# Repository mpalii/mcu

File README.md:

# MCUs

***ATmega8/*** folder is a multi-project solution for Microchip Studio IDE (Atmel Studio). Open the ***ATmega8.atsln*** file in Microchip Studio IDE (Atmel Studio), then rebuild the solution and all included projects will be ready to work.

### MCUs datasheets and documentation
- [ATmega8(L)](https://ww1.microchip.com/downloads/en/DeviceDoc/Atmel-2486-8-bit-AVR-microcontroller-ATmega8_L_datasheet.pdf)  
- [ATmega48A/PA/88A/PA/168A/PA/328/P](https://ww1.microchip.com/downloads/en/DeviceDoc/ATmega48A-PA-88A-PA-168A-PA-328-P-DS-DS40002061B.pdf)  
- [ATmega328P](https://ww1.microchip.com/downloads/en/DeviceDoc/Atmel-7810-Automotive-Microcontrollers-ATmega328P_Datasheet.pdf)  
- [AVR Instruction Set Manual](http://ww1.microchip.com/downloads/en/devicedoc/atmel-0856-avr-instruction-set-manual.pdf)  

### Troubleshoot  
#### 1. USBASP driver for Windows 10  
Operating system Windows requires driver for USBASP programmer. It is possible to use [libusb-win32](https://sourceforge.net/projects/libusb-win32/ "libusb-win32"), [libusbK](https://sourceforge.net/projects/libusbk/ "libusbK") or [Zadig](https://zadig.akeo.ie/ "Zadig"). Long story short, all these solutions install generic USB drivers.  
For 'libusbK': *step-1* download and install 'UsbK Development Kit' application; *step-2* plug USBASP programmer to USB; *step-3* launch 'Driver Install Creator Wizard'; *step-4* select 'libusbK' kernel driver package for target device and generate driver package; *step-5* install newly created driver from 'DriverPackages' folder; *step-6* remove 'UsbK Development Kit' and 'DriverPackages' folder.  
#### 2. USBASP connectivity issue with AVRdude  
Rootcause is a high internal clock frequency of a programmer. *First solution* is to specify baudrate with a '-B' flag:  
`avrdude -c usbasp -p m328p -B3` - this will set SCK frequency to 187500 Hz.  
*Second solution* is to close jumper JP3 in the USBASP device. No flags for avrdude is need in this case.  
#### 3. Visual Studio Code configuration  
To prepare VSC for working with avr-toolchai:  
- go to IntelliSense Configurations  
- hit the 'Add Configuration' button, type new configuration name (e.g. AVR) and hit 'Ok'  
- update 'Compiler path' input field with: *{path prefix}\toolchain\avr8\avr8-gnu-toolchain\bin\avr-gcc.exe*  
- add path to the 'Include path' input field: *{path prefix}/toolchain/avr8/avr8-gnu-toolchain/avr/include/\*\**  
- add *__AVR_ATmega328P__* to 'Defines' section  
#### 4. Atmel/Microchip Studio line numbers  
To show line numbers in A/M Studio go to **'Tools' -> 'Options' -> 'Text Editor' -> 'All Language'** and toggle **Line numbers** checkbox in the **Settings** section  

// TODO
https://avrdudes.github.io/avr-libc/avr-libc-user-manual/install_tools.html  
https://kleinembedded.com/stm32-without-cubeide-part-1-the-bare-necessities/#comment-37  
https://www.youtube.com/watch?v=7YhRFx-oyW4&list=PL3BR09unfgchRxdDws74aY4mlSk9eYGEs  
https://www.youtube.com/watch?v=MhOba73z-dQ&pp=ygUMYXJ0ZnVsIGJ5dGVz

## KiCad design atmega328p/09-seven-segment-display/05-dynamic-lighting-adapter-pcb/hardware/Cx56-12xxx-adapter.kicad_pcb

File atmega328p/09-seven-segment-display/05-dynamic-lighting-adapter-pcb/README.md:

### Example 05 - Cx56-12xxx adapter

PCB top:  

PCB bottom:  

Device:  

### Useful links

- [How to generate Gerber and Drill files in KiCad 7](https://jlcpcb.com/help/article/362-how-to-generate-gerber-and-drill-files-in-kicad-7)  
- [KiCAD 7 PCB Layout in 5 steps](https://www.youtube.com/watch?v=3FGNw28xBr0)

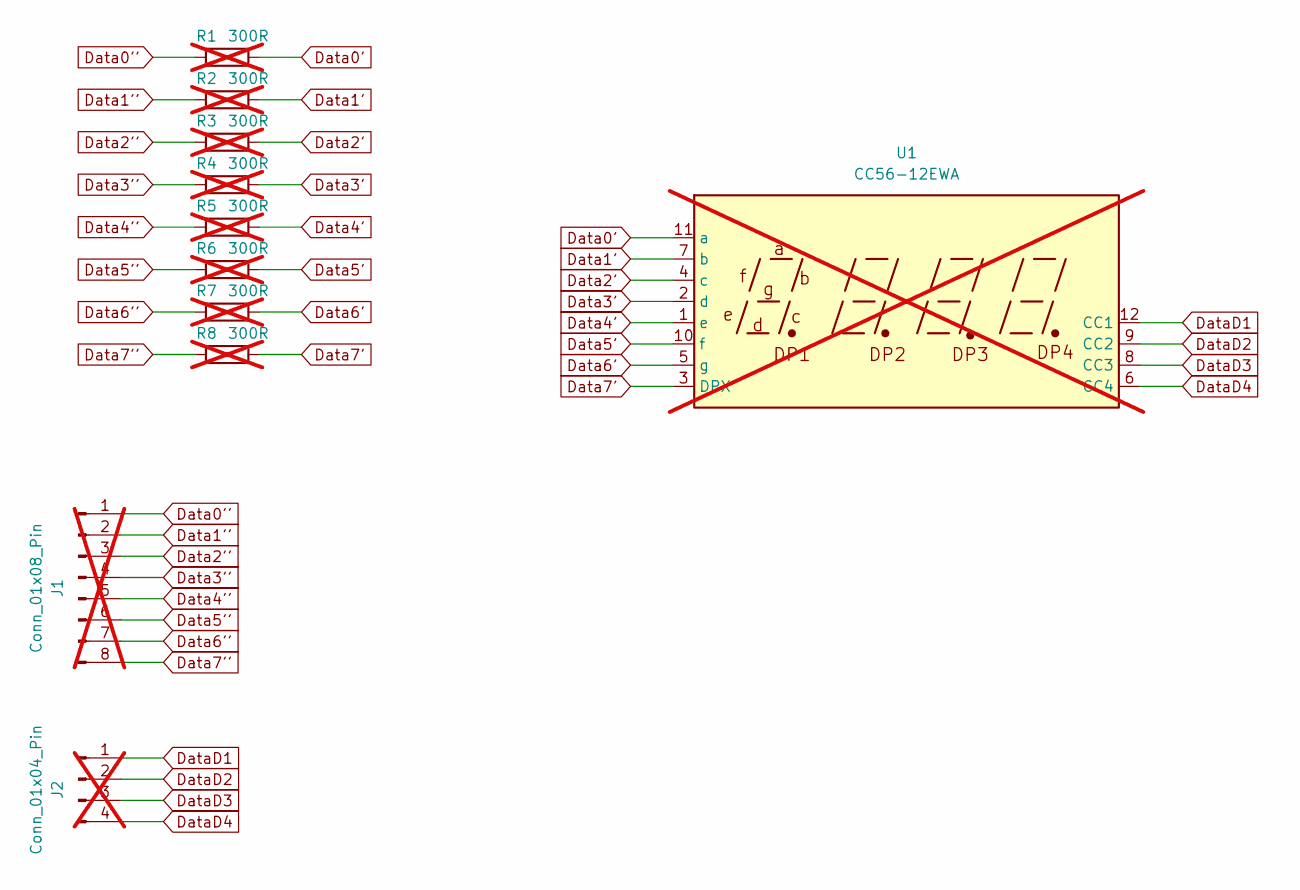
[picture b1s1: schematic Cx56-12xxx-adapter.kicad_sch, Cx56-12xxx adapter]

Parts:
J1: Conn_01x08_Pin; PinHeader_1x08_P2.54mm_Vertical; not fitted
J2: Conn_01x04_Pin; PinHeader_1x04_P2.54mm_Vertical; not fitted
R1, R2, R3, R4, R5, R6, R7, R8: 300R; R_0805_2012Metric_Pad1.20x1.40mm_HandSolder; not fitted
U1: CC56-12EWA; CA56-12EWA; not fitted

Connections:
Data0': R1.1, U1.11 (a)
Data0'': J1.1, R1.2
Data1': R2.1, U1.7 (b)
Data1'': J1.2, R2.2
Data2': R3.1, U1.4 (c)
Data2'': J1.3, R3.2
Data3': R4.1, U1.2 (d)
Data3'': J1.4, R4.2
Data4': R5.1, U1.1 (e)
Data4'': J1.5, R5.2
Data5': R6.1, U1.10 (f)
Data5'': J1.6, R6.2
Data6': R7.1, U1.5 (g)
Data6'': J1.7, R7.2
Data7': R8.1, U1.3 (DPX)
Data7'': J1.8, R8.2
DataD1: J2.1, U1.12 (CC1)
DataD2: J2.2, U1.9 (CC2)
DataD3: J2.3, U1.8 (CC3)
DataD4: J2.4, U1.6 (CC4)

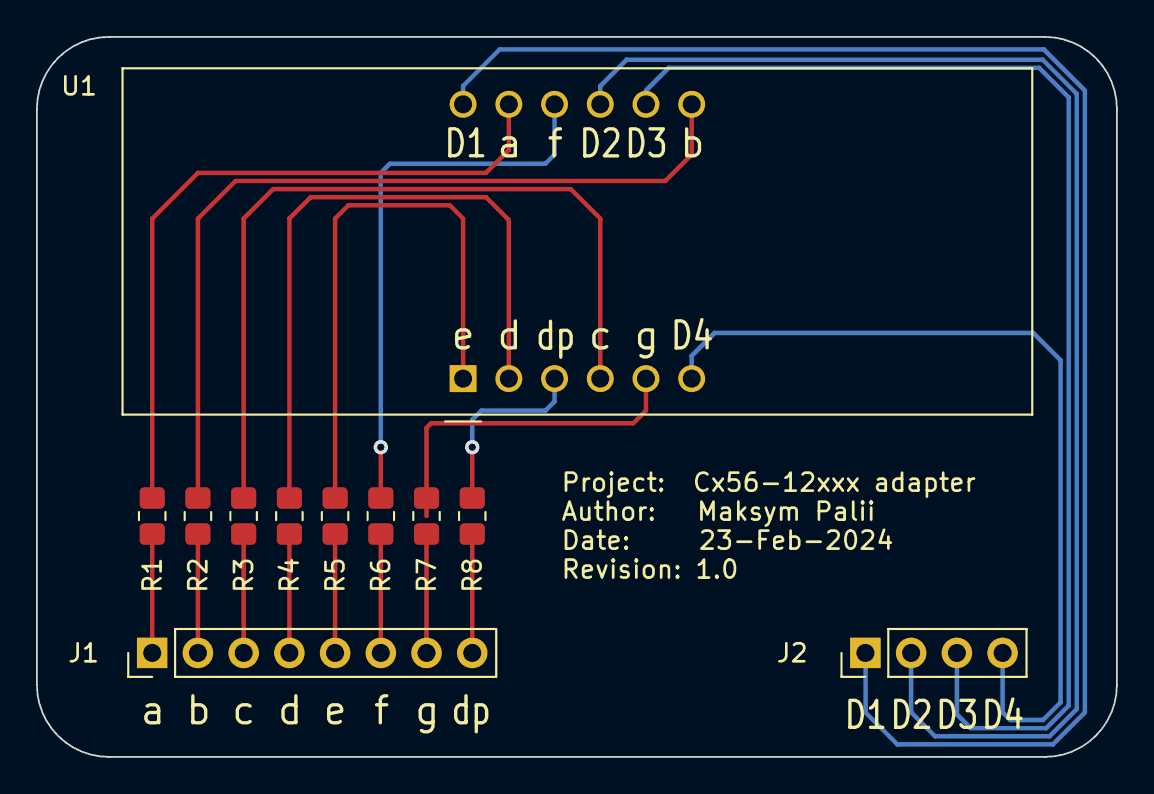
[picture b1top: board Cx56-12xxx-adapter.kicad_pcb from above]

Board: 2 copper layers, 60.0 x 40.0 mm, 11 parts (0 on the bottom side), 20 nets.

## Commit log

2023-05-21 Hello World - bare metal
2023-05-21 Type layout
2023-05-21 Hello World - description adjustment
2023-05-21 Type layout - description adjustment
2023-05-21 Type layout - main.c adjustment
2023-05-21 Type layout - Makefile adjustment
2023-05-27 Little endian
2023-06-04 Delay and fuses configuration
2023-06-04 Timer 0 - precise generator
2023-06-05 Fuses. delay example adjustment
2023-06-10 Timer 0 example - precise timing
2023-06-18 Multitasking example, round robin scheduler
2023-06-18 UART, speed test, lightweight logger
2023-06-18 Multitasking description adjustment
2023-06-29 LCD 1602
2023-06-29 Buzzer, timer 2, frequency generator without interrupts
2023-07-08 EEPROM memory
2023-07-08 Timer/Counter 1, random number generator
2023-07-09 Type Layout - enum example
2023-07-09 GPIO driver - macro approach
2023-09-05 Non-blocking LCD 1602 output
2023-12-14 Disabled compiler optimization
2023-12-14 Added '*.json' to .gitignore
2024-01-14 LICENCE adjustment
2024-01-14 Timers
2024-01-18 Added c_cpp_properties.json file content
2024-01-21 m328p-00: bare metal 'Hello World'
2024-01-21 m328p-01: type layout
2024-01-21 VS code configuration file
2024-01-21 m328p-02: endianess
2024-01-21 m328p-03: fuses, delay
2024-01-21 m328p-04: Timer/Counter 0, precise timing
2024-01-28 m328p-05: button, internal pull-up
2024-01-28 m328p-05: button, internal pull-up, RC debounce
2024-01-28 m328p-05: button, external pull-up
2024-01-28 m328p-05: button, internal pull-up, 'main.c' description fix
2024-01-28 m328p-05: button, external pull-up, RC debounce
2024-01-28 m328p-05: button, internal pull-up, RC debounce, fix connections
2024-01-28 m328p-05: button, external pull-up, RC debounce, fix connections
2024-01-29 m328p-05: schematic fixes
2024-01-29 m328p-05: button, external pull-down
2024-01-29 m328p-05: button, external pull-down, RC debounce
2024-01-30 m328p-05: scheme adjustment, changed structure
2024-02-01 m328p-05: software debounce
2024-02-04 m328p-06: electromagnetic interference EMI
2024-02-05 m328p-00: documentation section fix
2024-02-10 m328p-07: multitasking
2024-02-11 m328p-08: GPIO driver
2024-02-14 m328p-09: seven-segment display with common cathode, static lighting
2024-02-14 m328p-09: seven-segment display with common anode, static lighting
2024-02-14 m328p-09: 'main.c' typo fix
2024-02-17 GPIO driver example clean up
2024-02-26 m328p-09: seven-segment display dynamic lighting common cathode
2024-02-26 m328p-09: seven-segment display dynamic lighting universal driver
2024-03-23 m328p-10: external interrupts queue and priorities
2024-03-23 m328p-11: sn74hc595 examples
2024-03-23 m328p-09: pin reassignment
2024-03-26 m328p-05: matrix keyboard
2024-03-26 m328p-05: matrix keyboard - DRY pattern
2024-03-26 m328p: fix hardware pin mapping - external oscillator
2024-03-30 m328p-05: simulation schemes adjustment
2024-03-30 m328p-08: gpio driver refactoring
2024-03-31 Include KiCad specific files to .gitignore
2024-04-03 m328p-09: dynamic lighting adapter (4 digit display)
2024-04-04 m328p-11: 4x4 led matrix, static lighting, with minimalistic font
2024-04-05 m328p-11: font fixes
2024-04-05 m328p-11: led matrix 64x8 with dynamic lighting
2024-04-05 m328p-09: PCB layout tips
2024-04-09 m328p-12: frequency meter with external interrupt
2024-04-26 m328p-09: simulation scheme fix
2024-04-26 m328p-12: frequency meter with timer-1 input capture mide
2024-04-29 m328p-13: timer 2 buzzer
2024-04-29 Old timer 2 buzzer example decommissioning
2024-05-09 m328p-14: ADC single conversion mode
2024-05-09 m328p-14: ADC free running mode
2024-05-11 m328p-14: ADC auto triggering mode
2024-05-12 m328p-14: SMA filter
2024-05-18 m328p-14: ADC and TMP36 analog temperature sensor
2024-05-19 m328p-15: analog comparator, default mode
2024-05-19 m328p-15: analog comparator, fixed bandgap reference voltage (1.1 V)
2024-05-19 m328p-15: analog comparator, ADC multiplexed input
2024-05-23 m328p-16: EEPROM read/write
2024-05-23 m328p-16: configuration with EEPROM, function pointer
2024-06-02 m328p-17: LCD1602 8bit mode
2024-06-15 m328p-17: LCD1602 4bit mode
2024-06-28 m328p-17: LCD1602 8bit mode (refactoring)
2024-06-28 m328p-17: LCD1602 4bit mode (refactoring)
2024-06-28 m328p-17: LCD1602 internal characters
2024-06-28 m328p-17: LCD1602 custom characters
2024-06-28 m328p-17: LCD1602 addresses
2024-06-28 m328p-17: LCD1602 02-4bit-data-bus example deletion
2024-06-29 m328p-17: LCD1602 non blocking approach
2024-06-30 m328p-17: LCD1602 extra commands
2024-07-06 m328p-17: LCD1602 formatting and floating point
2024-07-07 m328p-17: LCD1602 TMP32 noise cancelling (draft)
2024-07-14 m328p-17: LCD1602 TMP32
2024-07-26 m328p-18: Timer 0 - fast PWM
2024-07-26 m328p-18: Timer 1 - fast PWM
2024-07-26 m328p-18: Timer 1 - phase correct PWM
2024-07-26 m328p-18: Timer 1 - phase and frequency correct PWM
2024-07-26 m328p-18: rotary encoder
2024-07-31 m328p-19: 28BYj-48 step motor with ULN2003
2024-08-03 m328p-20: UART byte-oriented
2024-08-03 m328p-20: UART file-oriented
2024-08-03 m328p-20: UART non blocking (interrupt based)
2024-08-03 m328p-20: UART speed test 8MHz, sprintf
2024-08-04 m328p-20: UART speed test 18432kHz, itoa
2024-08-04 m328p-20: UART lightweight logger
2024-08-04 m328p-20: UART bit-banging
2024-08-04 Incorrect package removing
2024-08-05 m328p-21: 1-wire interface, presence procedure
2024-08-09 m328p-21: 1-wire interface, prototype
2024-08-10 m328p-21: 1-wire interface, device identification
2024-08-10 m328p-21: 1-wire interface, bus check
2024-08-10 m328p-21: 1-wire interface, single slave
2024-08-10 m328p-21: 1-wire interface, multiple slaves
2024-08-11 m328p-21: 1-wire interface, cyclic redundancy check
2024-08-11 m328p-21: description file adjustment
2024-08-11 m328p-21: DRAFT deletion
2024-08-15 m644-00: general description
2024-08-17 m644-01: GPIO driver
2024-08-17 m644-02: TWI(I2C) eeprom 24C02
2024-08-18 m644-02: TWI(I2C) bus scanner
2024-08-20 m644-02: TWI(I2C) eeprom 24C256
2024-08-24 m644-02: SHT3x sensor Single Shot Data Acquisition Mode, Clock Stretching
2024-08-24 m644-02: SHT3x sensor Single Shot Data Acquisition Mode, No Clock Stretching
2024-09-07 m644-03: DDS - timer0 pwm
2024-09-07 m644-02: TWI(I2C) oled 128x64
2024-09-07 m644-03: DDS - sine lookup table
2024-09-07 m644-03: DDS - relative sine lookup table
2024-09-07 m644-03: DDS - relative sine signal generation
2024-09-07 m644-03: DDS - absolute sine signal generation
2024-09-09 m644-03: DDS - signal synthesis
2024-09-10 m644-03: DDS - signal synthesis 18.432MHz
2024-09-12 m644-03: DDS - signal synthesis 18.432MHz optimization
2024-09-14 m644-03: DDS - additive synthesis
2024-09-15 m644-03: DDS - white noice
2024-09-16 m644-03: DDS - sine lut (refactoring)
2024-09-20 m644-03: sinewave generating with exponential rise
2024-09-21 m644-04: exponential rise DAC
2024-09-21 m644-04: exponential fall DAC
2024-09-21 m644-04: exponential rise and fall DAC
2024-09-21 m644-04: attack adjustment
2024-09-21 m644-03: decay
2024-09-21 m644-03: attack and decay
2024-09-21 m644-03: attack and decay (ISR_NAKED)
2024-09-22 m644-03: FM frequency modulation
2024-09-23 m644-03: FM frequency modulation (adjustment)
2024-09-28 m644-15: triangle and sawtooth lookup tables
2024-09-29 m644-16: additive synthesis with noise
2024-10-06 m644-17: audio sequencer
2024-10-07 m8-00: migration from old repository
2024-10-08 m328p-05: debounce scheme
2024-10-08 m328p-00: drafts migration from old repository
2024-10-08 ece4760 old catalogs consolidation
2024-10-08 README.md adjustment
2024-10-10 ece4760-00: ATmega644 GPIO driver
2024-10-10 ece4760-00: ATmega644 GPIO driver deletion
2024-10-10 ece4760-01: scheduler
2024-10-11 ece4760-02: timers
2024-10-12 ece4760-03: lcd
2024-10-12 ece4760-04: eeprom
2024-10-12 ece4760-05: debounce
2024-10-13 rtm-00: initial commit
2024-10-13 rtm-01: GPIO driver
2024-10-13 rtm-02: YL-34 built-in led
2024-10-13 rtm-03: GPIO driver refactoring with incapsulation
2024-10-13 rtm-04: UART driver
2024-10-13 rtm-05: Timer0 driver
2024-10-13 rtm-06: GPIO driver refactoring (exclude incapsulation)
2024-10-13 rtm-06: Timer2 driver
2024-10-13 rtm-07: LED driver
2024-10-14 rtm-08: button driver
2024-10-14 rtm-09: reset driver, button driver fixes
2024-10-14 rtm-09: Timer1 driver
2024-10-14 rtm-10: LCD1602 driver
2024-10-14 rtm-11: extra logging, drivers rearrangement, UART speed increasing
2024-10-18 rtm-12: DRAFT
2024-10-19 rtm-13: working prototype
2024-10-19 rtn-13: logs and messages consolidation
2024-10-19 rtm-14: non blocking UART
2024-10-22 rtm-15: system stabilization
2024-10-22 rtm-16: components renaming
2024-10-23 rtm-17: eeprom, high score saving
2024-10-23 rtm-18: messages adjustment
2024-10-23 rtm-19: removed PRE_MEASUREMENT state
2024-10-23 rtm-20: packages rearrangement
2024-10-24 rtm-21: serial input handling
2024-10-24 rtm-22: reduction of measurement error
2024-10-24 rtm-23: naming changes
2024-10-25 rtm-24: task deadline execution test - FAILED (heavy sprintf)
2024-10-25 rtm-25: fix scheduler collapse
2024-10-25 rtm-26: measurement error reducing
2024-10-25 rtm-27: calibration tool
2024-10-25 rtm-28: clean up
2024-10-26 m644-18: lcd1602 driver (4bit mode)
2024-10-26 m644-19: button state machine
2024-10-26 ece4760-06: ADC
2024-10-27 ece4760-07: ADC precise
2024-11-06 rtm-29: calibration tool adjustment
2024-11-06 rtm-30: high precision approach
2024-11-07 rtm-31: return stdio.h
2024-11-07 rtm-32: clean up
2024-12-15 ece4760-08: header fix
2024-12-22 dmm-01: resistance measurement
2024-12-22 dmm-02: resistance measurement, 10k limit
2024-12-28 dmm-03: calibration
2024-12-29 dmm-04: calibration - ADC offset
2024-12-29 dmm-04: calibration - ADC offset, 2
2024-12-29 dmm-05:resistance measurement, 100k limit
2025-01-05 dmm-06: attempt to fix stability (not worked)
2025-01-05 m328p-22: bootloader (draft)
2025-01-05 m328p-22: bootloader (PC part)
